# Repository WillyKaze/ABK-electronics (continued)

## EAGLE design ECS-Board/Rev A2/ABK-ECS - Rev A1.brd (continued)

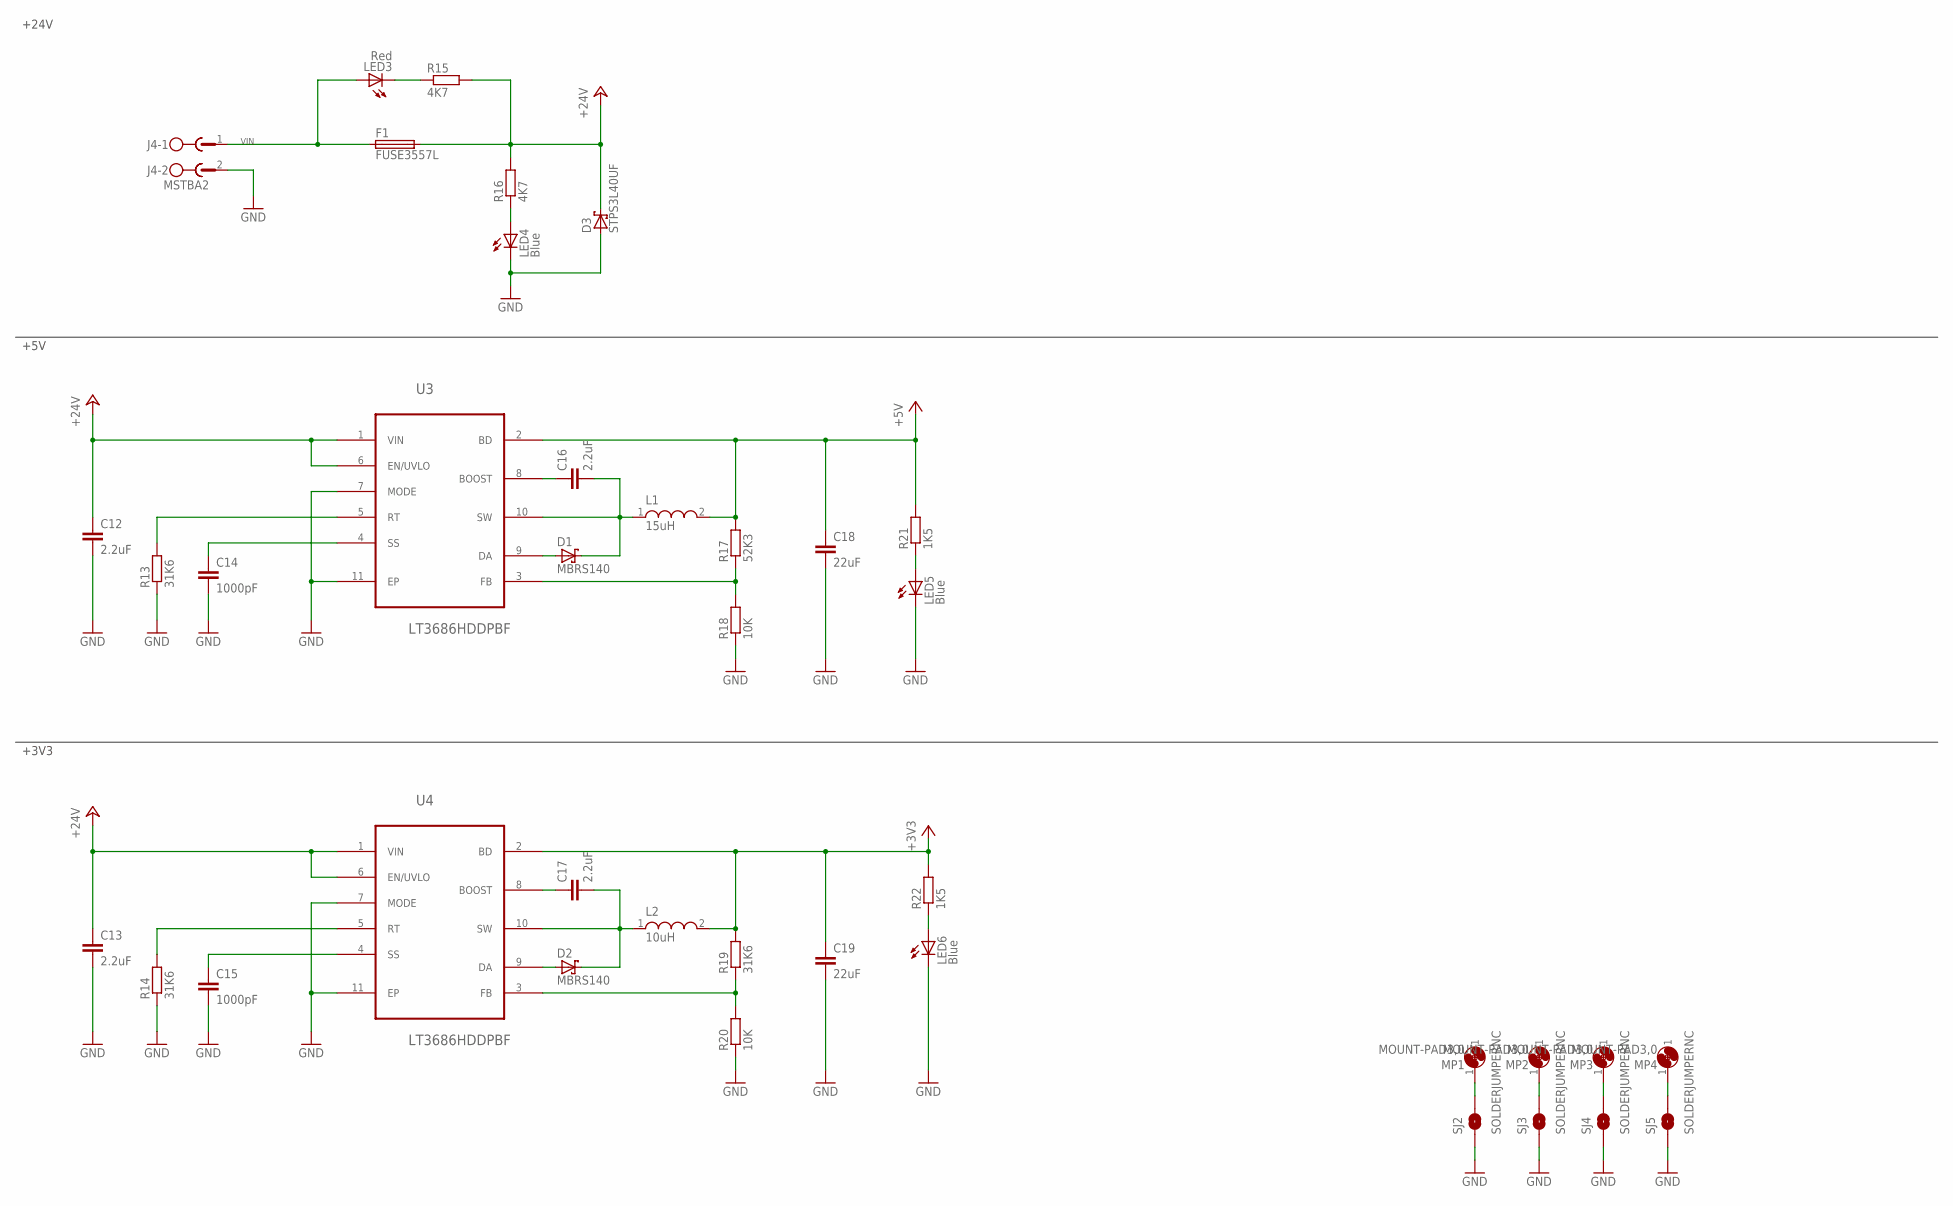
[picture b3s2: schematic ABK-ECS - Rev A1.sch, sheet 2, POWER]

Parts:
C12, C13, C16, C17: 2.2uF; C0603; MPN GRT188R61H225KE13D
C14, C15: 1000pF; C0603; MPN MC0603B102K500CT
C18, C19: 22uF; C0805; MPN MCMT21N220F250CT
D1, D2: MBRS140; DO-214AA; MPN MBRS140T3G
D3: STPS3L40UF; SMB
F1: FUSE3557L; 3557-LITTLE; MPN 3557
J4: MSTBA2
L1: 15uH; WE-PD2_5848/5820; MPN 744774115
L2: 10uH; WE-PD2_5848/5820; MPN 74477410
LED3: Red; CHIPLED_0603; MPN OVS-0603
LED4: Blue; CHIPLED_0603; MPN OVS-0603
LED5, LED6: Blue; CHIP-LED0603; MPN OVS-0603
MP1, MP2, MP3, MP4: MOUNT-PAD3,0; P3,0
R13, R14, R19: 31K6; R0603; MPN MCMR06X3162FTL
R15, R16: 4K7; R0603; MPN MCMR06X4701FTL
R17: 52K3; R0603; MPN MC0063W0603152K3
R18, R20: 10K; R0603; MPN MCMR06X1002FTL
R21, R22: 1K5; R0603; MPN MCMR06X1501FTL
SJ2, SJ3, SJ4, SJ5: SOLDERJUMPERNC; SJ_2S
U3, U4: LT3686HDDPBF; DFN300X300X80-11N

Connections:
1: MP1.1, SJ2.2
2: MP2.1, SJ3.2
3: MP3.1, SJ4.2
4: MP4.1, SJ5.2
+3V3: C19.1, L2.2, R19.2, R22.2, U4.2 (BD); also elsewhere on the board
+5V: C18.1, L1.2, R17.2, R21.2, U3.2 (BD); also elsewhere on the board
+24V: C12.1, C13.1, D3.C, F1.3 (2), F1.4 (2), R15.2, R16.2, U3.1 (VIN), U3.6 (EN/UVLO), U4.1 (VIN), U4.6 (EN/UVLO); also elsewhere on the board
GND: C12.2, C13.2, C14.2, C15.2, C18.2, C19.2, D3.A, J4.2, LED4.C, LED5.C, LED6.C, R13.1, R14.1, R18.1, R20.1, SJ2.1, SJ3.1, SJ4.1, SJ5.1, U3.7 (MODE), U3.11 (EP), U4.7 (MODE), U4.11 (EP); also elsewhere on the board
unnamed: R13.2, U3.5 (RT)
unnamed: C14.1, U3.4 (SS)
unnamed: R14.2, U4.5 (RT)
unnamed: C15.1, U4.4 (SS)
unnamed: R17.1, R18.2, U3.3 (FB)
unnamed: C16.1, U3.8 (BOOST)
unnamed: C16.2, D1.C, L1.1, U3.10 (SW)
unnamed: D1.A, U3.9 (DA)
unnamed: R19.1, R20.2, U4.3 (FB)
unnamed: C17.1, U4.8 (BOOST)
unnamed: C17.2, D2.C, L2.1, U4.10 (SW)
unnamed: D2.A, U4.9 (DA)
unnamed: LED4.A, R16.1
unnamed: LED3.C, R15.1
unnamed: LED6.A, R22.1
unnamed: LED5.A, R21.1
VIN: F1.1, F1.2 (1), J4.1, LED3.A

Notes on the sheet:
+5V
+3V3
+24V

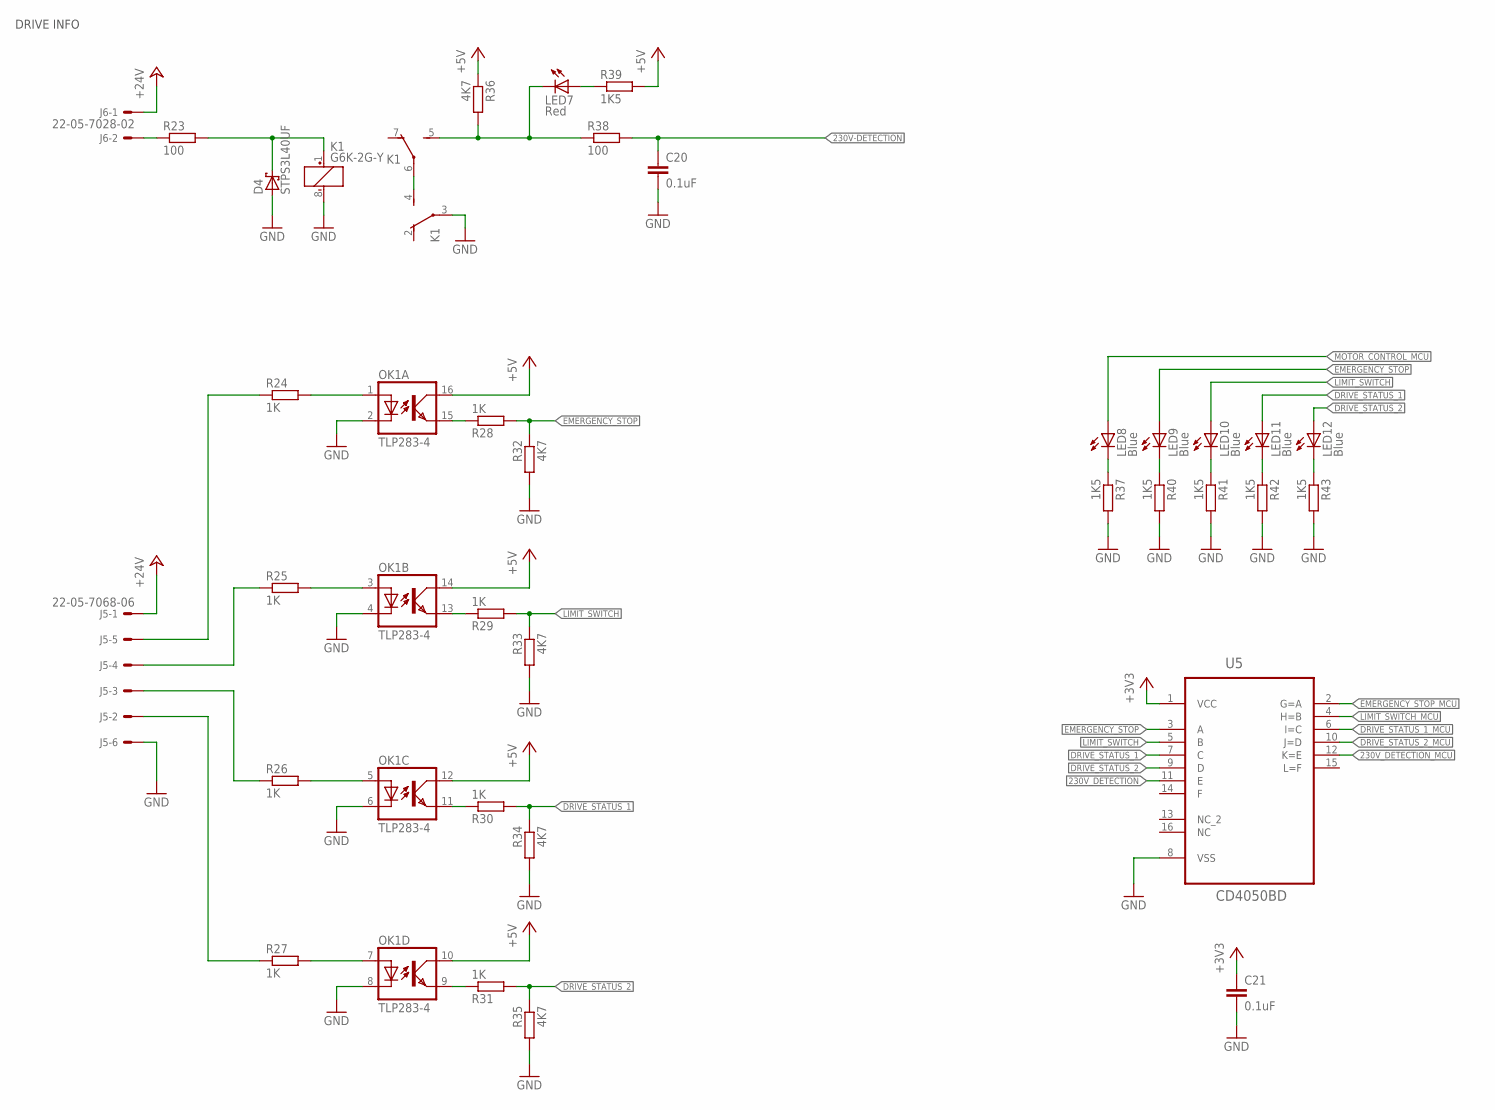
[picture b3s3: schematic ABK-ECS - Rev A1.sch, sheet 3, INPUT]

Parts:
C20, C21: 0.1uF; C0603; MPN MC0603B104K160CT
D4: STPS3L40UF; SMB
J5: 22-05-7068-06; 7395-06; MPN 22-05-7068
J6: 22-05-7028-02; 7395-02; MPN 22-05-7028
K1: G6K-2G-Y; MPN G6K-2G-Y 24DC
LED7: Red; CHIPLED_0603; MPN OVS-0603
LED8, LED9, LED10, LED11, LED12: Blue; CHIPLED_0603; MPN OVS-0603
OK1: TLP283-4; MINI-FLAT-16; MPN TCMT4100
R23, R38: 100; R0603; MPN MCMR06X1000FTL
R24, R25, R26, R27, R28, R29, R30, R31: 1K; R0603; MPN MCMR06X1001FTL
R32, R33, R34, R35, R36: 4K7; R0603; MPN MCMR06X4701FTL
R37, R39, R40, R41, R42, R43: 1K5; R0603; MPN MCMR06X1501FTL
U5: CD4050BD; SOIC127P600X175-16N

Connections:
230V-DETECTION: C20.1, R38.2; also elsewhere on the board
230V_DETECTION: U5.11 (E)
230V_DETECTION_MCU: U5.12 (K=E); also elsewhere on the board
+3V3: C21.1, U5.1 (VCC); also elsewhere on the board
+5V: OK1.10 (COL), OK1.12 (COL), OK1.14 (COL), OK1.16 (COL), R36.1, R39.2; also elsewhere on the board
+24V: J5.1, J6.1; also elsewhere on the board
DRIVE_STATUS_1: LED11.A, R30.2, R34.1, U5.7 (C)
DRIVE_STATUS_1_MCU: U5.6 (I=C); also elsewhere on the board
DRIVE_STATUS_2: LED12.A, R31.2, R35.1, U5.9 (D)
DRIVE_STATUS_2_MCU: U5.10 (J=D); also elsewhere on the board
EMERGENCY_STOP: LED9.A, R28.2, R32.1, U5.3 (A)
EMERGENCY_STOP_MCU: U5.2 (G=A); also elsewhere on the board
GND: C20.2, C21.2, D4.A, J5.6, K1.3, K1.8 (-), OK1.2 (C), OK1.4 (C), OK1.6 (C), OK1.8 (C), R32.2, R33.2, R34.2, R35.2, R37.2, R40.2, R41.2, R42.2, R43.2, U5.8 (VSS); also elsewhere on the board
LIMIT_SWITCH: LED10.A, R29.2, R33.1, U5.5 (B)
LIMIT_SWITCH_MCU: U5.4 (H=B); also elsewhere on the board
MOTOR_CONTROL_MCU: LED8.A; also elsewhere on the board
unnamed: D4.C, K1.1 (+), R23.2
unnamed: J6.2, R23.1
unnamed: OK1.1 (A), R24.2
unnamed: OK1.3 (A), R25.2
unnamed: OK1.5 (A), R26.2
unnamed: OK1.7 (A), R27.2
unnamed: J5.2, R27.1
unnamed: J5.3, R26.1
unnamed: J5.4, R25.1
unnamed: J5.5, R24.1
unnamed: LED8.C, R37.1
unnamed: LED9.C, R40.1
unnamed: LED10.C, R41.1
unnamed: LED11.C, R42.1
unnamed: K1.4 (S), K1.6
unnamed: OK1.9 (EMIT), R31.1
unnamed: OK1.11 (EMIT), R30.1
unnamed: OK1.13 (EMIT), R29.1
unnamed: OK1.15 (EMIT), R28.1
unnamed: LED12.C, R43.1
unnamed: K1.5 (S), LED7.C, R36.2, R38.1
unnamed: LED7.A, R39.1

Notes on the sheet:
DRIVE INFO

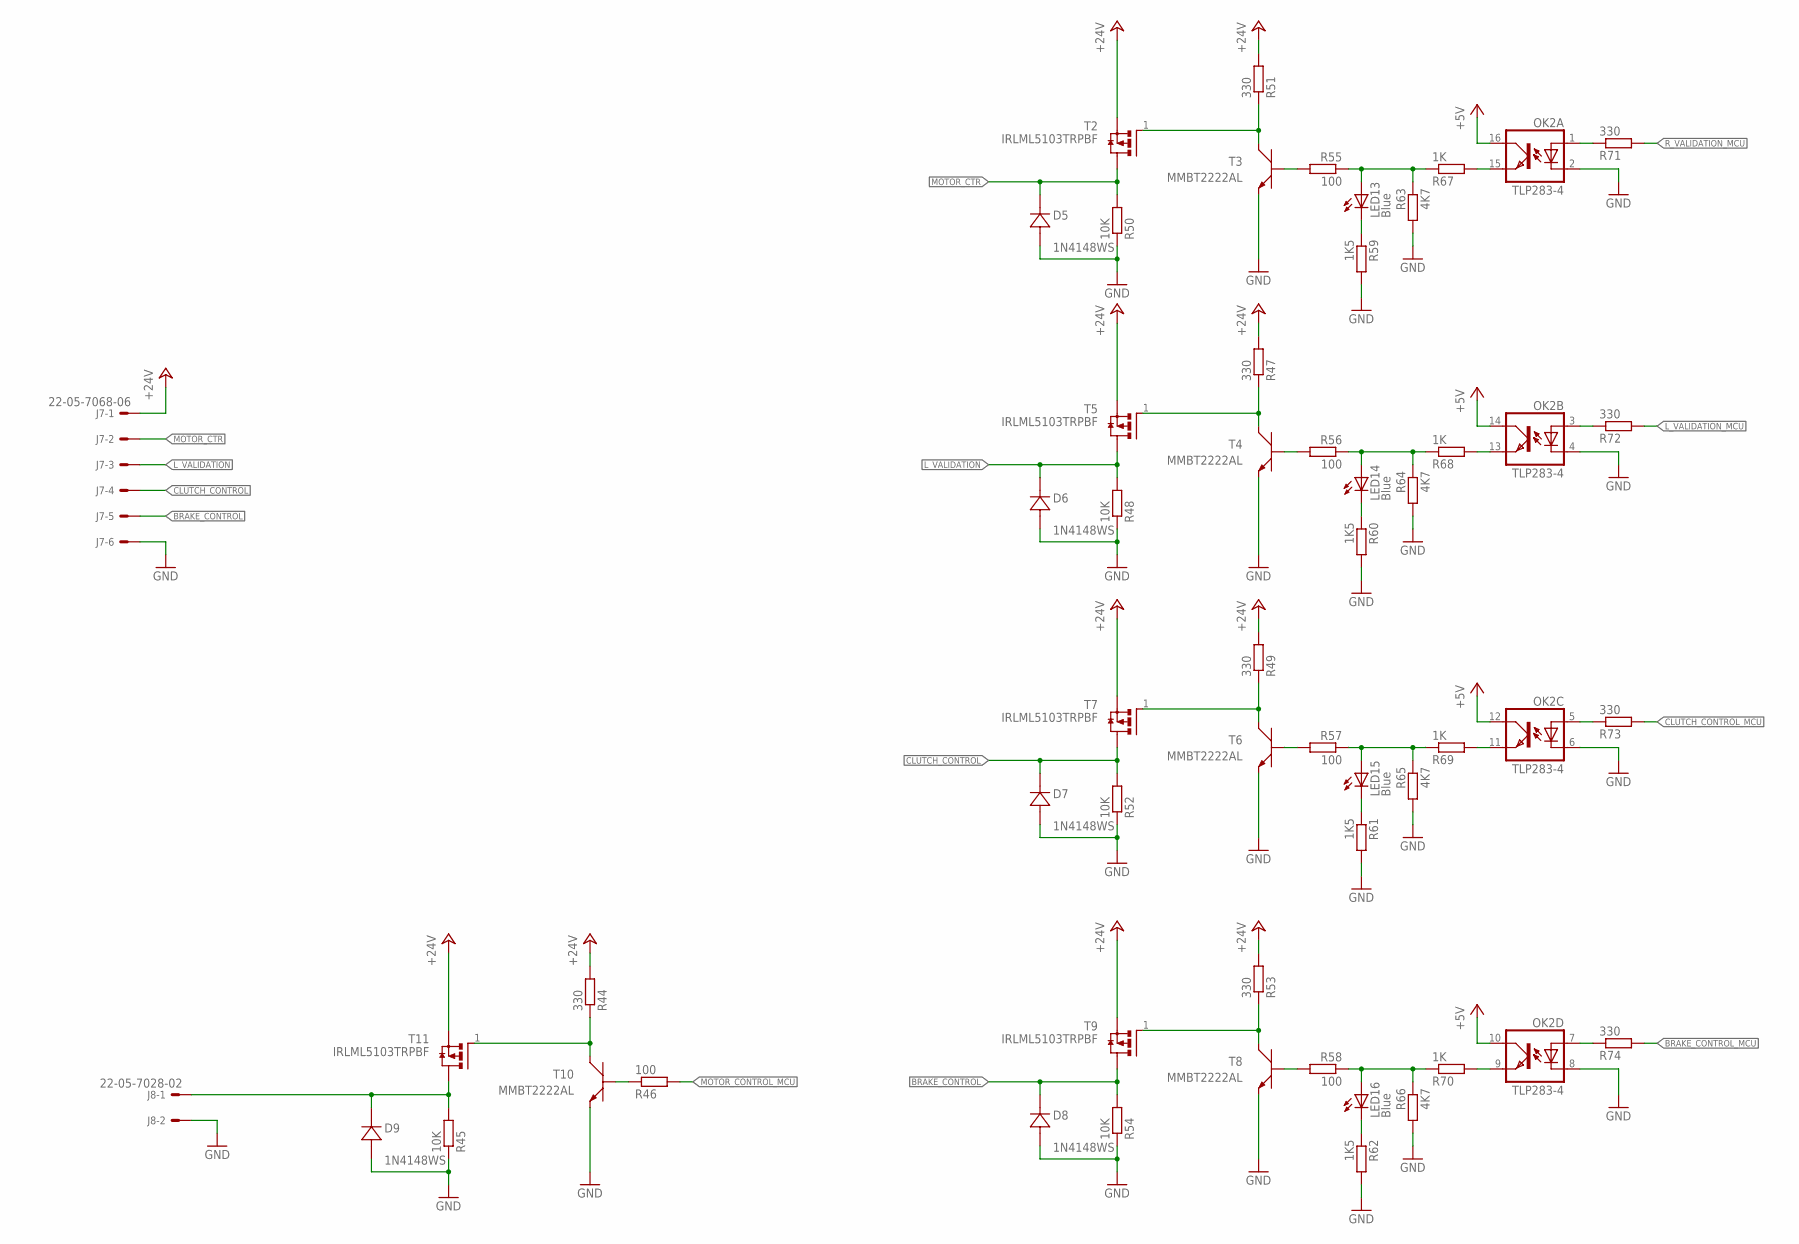
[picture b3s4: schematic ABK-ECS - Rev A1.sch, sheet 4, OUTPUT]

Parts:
D5, D6, D7, D8, D9: 1N4148WS; SOD323-W
J7: 22-05-7068-06; 7395-06; MPN 22-05-7068
J8: 22-05-7028-02; 7395-02; MPN 22-05-7028
LED13, LED14, LED15, LED16: Blue; CHIPLED_0603; MPN OVS-0603
OK2: TLP283-4; MINI-FLAT-16; MPN TCMT4100
R44, R47, R49, R51, R53: 330; R0603; MPN MCMR06X4701FTL
R45, R48, R50, R52, R54: 10K; R0603; MPN MCMR06X4701FTL
R46, R55, R56, R57, R58: 100; R0603; MPN MCMR06X1000FTL
R59, R60, R61, R62: 1K5; R0603; MPN MCMR06X1501FTL
R63, R64, R65, R66: 4K7; R0603; MPN MCMR06X4701FTL
R67, R68, R69, R70: 1K; R0603; MPN MCMR06X1001FTL
R71, R72, R73, R74: 330; R0603; MPN MCMR06X3300FTL
T2, T5, T7, T9, T11: IRLML5103TRPBF; SOT95P240X112-3N
T3, T4, T6, T8, T10: MMBT2222AL; SOT−23

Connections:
+5V: OK2.10 (COL), OK2.12 (COL), OK2.14 (COL), OK2.16 (COL); also elsewhere on the board
+24V: J7.1, R44.2, R47.2, R49.2, R51.2, R53.2, T2.2 (S), T5.2 (S), T7.2 (S), T9.2 (S), T11.2 (S); also elsewhere on the board
BRAKE_CONTROL: D8.C (1), J7.5, R54.2, T9.3 (D)
BRAKE_CONTROL_MCU: R74.2; also elsewhere on the board
CLUTCH_CONTROL: D7.C (1), J7.4, R52.2, T7.3 (D)
CLUTCH_CONTROL_MCU: R73.2; also elsewhere on the board
GND: D5.A (2), D6.A (2), D7.A (2), D8.A (2), D9.A (2), J7.6, J8.2, OK2.2 (C), OK2.4 (C), OK2.6 (C), OK2.8 (C), R45.1, R48.1, R50.1, R52.1, R54.1, R59.2, R60.2, R61.2, R62.2, R63.2, R64.2, R65.2, R66.2, T3.2 (E), T4.2 (E), T6.2 (E), T8.2 (E), T10.2 (E); also elsewhere on the board
L_VALIDATION: D6.C (1), J7.3, R48.2, T5.3 (D)
L_VALIDATION_MCU: R72.2; also elsewhere on the board
MOTOR_CONTROL_MCU: R46.2; also elsewhere on the board
MOTOR_CTR: D5.C (1), J7.2, R50.2, T2.3 (D)
unnamed: R55.2, T3.1 (B)
unnamed: R51.1, T2.1 (G), T3.3 (C)
unnamed: R56.2, T4.1 (B)
unnamed: R47.1, T4.3 (C), T5.1 (G)
unnamed: R57.2, T6.1 (B)
unnamed: R49.1, T6.3 (C), T7.1 (G)
unnamed: R58.2, T8.1 (B)
unnamed: R53.1, T8.3 (C), T9.1 (G)
unnamed: R46.1, T10.1 (B)
unnamed: R44.1, T10.3 (C), T11.1 (G)
unnamed: D9.C (1), J8.1, R45.2, T11.3 (D)
unnamed: LED13.A, R55.1, R63.1, R67.1
unnamed: OK2.15 (EMIT), R67.2
unnamed: LED14.A, R56.1, R64.1, R68.1
unnamed: OK2.13 (EMIT), R68.2
unnamed: LED15.A, R57.1, R65.1, R69.1
unnamed: LED16.A, R58.1, R66.1, R70.1
unnamed: OK2.11 (EMIT), R69.2
unnamed: OK2.9 (EMIT), R70.2
unnamed: OK2.1 (A), R71.1
unnamed: OK2.3 (A), R72.1
unnamed: OK2.7 (A), R74.1
unnamed: OK2.5 (A), R73.1
unnamed: LED13.C, R59.1
unnamed: LED14.C, R60.1
unnamed: LED15.C, R61.1
unnamed: LED16.C, R62.1
R_VALIDATION_MCU: R71.2; also elsewhere on the board

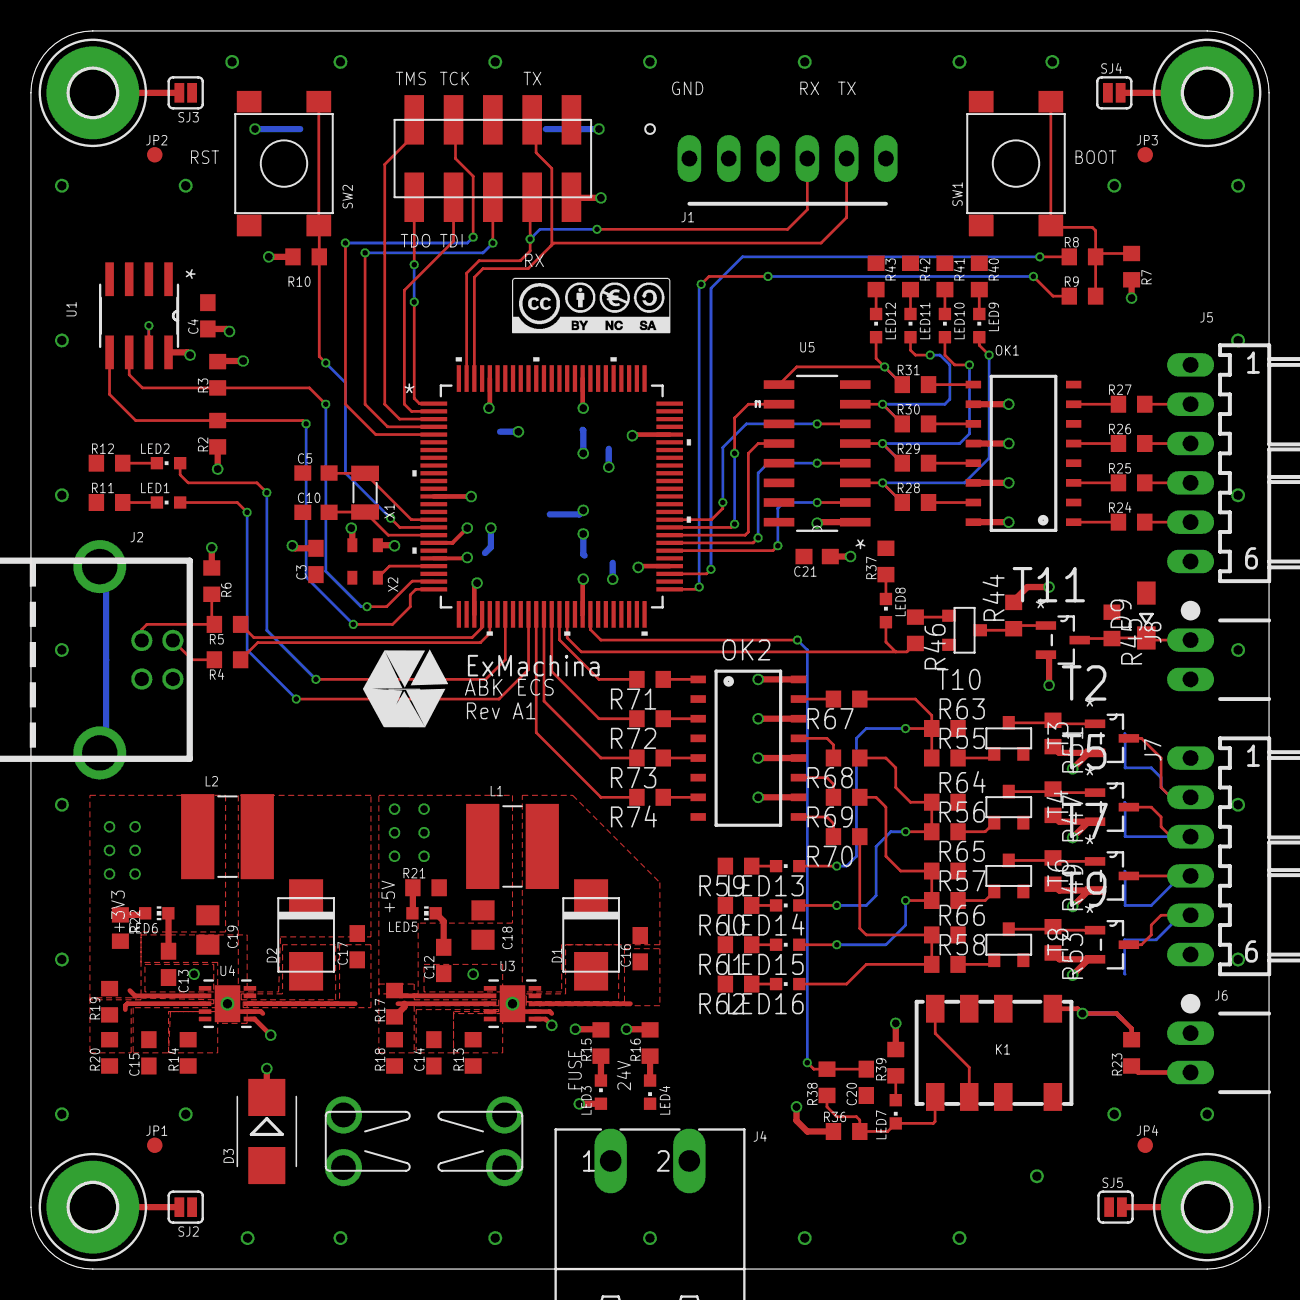
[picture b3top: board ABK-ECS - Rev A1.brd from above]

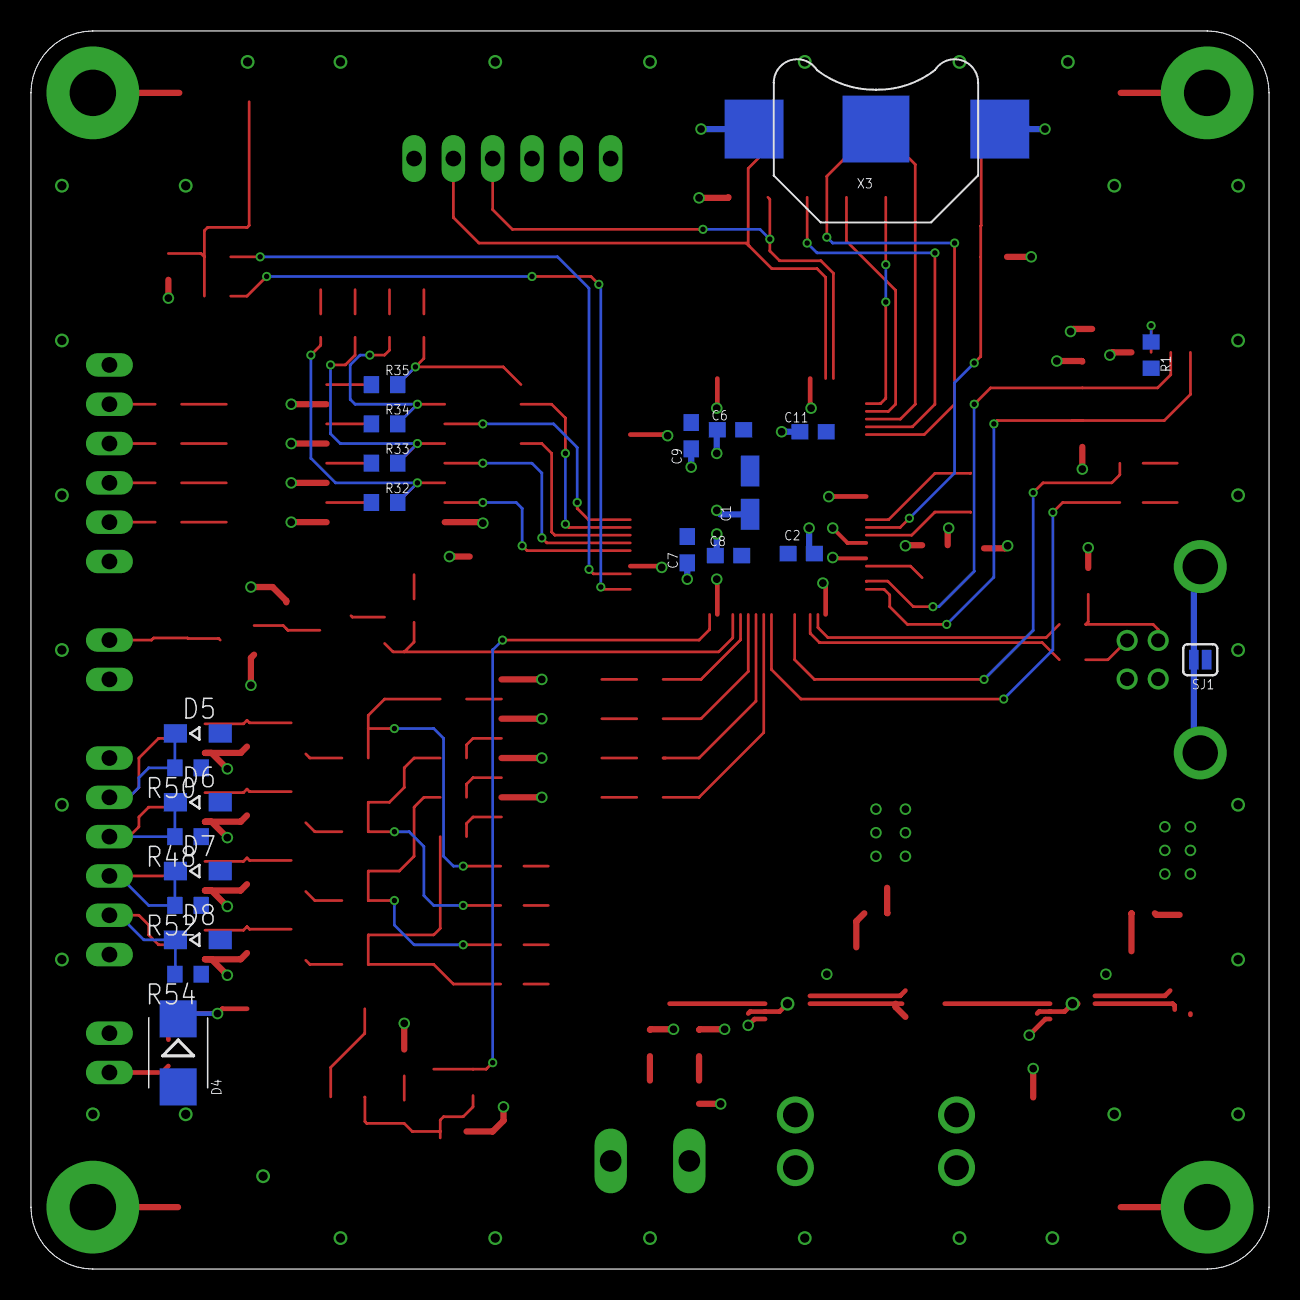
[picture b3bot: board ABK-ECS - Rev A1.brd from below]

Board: 4 copper layers, 80.0 x 80.0 mm, 169 parts (23 on the bottom side), 121 nets.

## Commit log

2017-02-28 Clean repos
2017-02-28 Rename folder
2017-02-28 Change readme and description files
2017-03-07 Update MPN and generate part list
2017-05-30 Update MDP folder
2017-05-30 Modify ECS board with pull-down output
2017-07-18 Add rev A2 and modify board
2017-08-31 Add input and output to the board and LDO 5V to 3.3V for FTDI connector
2017-09-05 Rotate board 90 degres
2017-09-05 Add 24V and Vin poly for the fuse
2017-09-05 Add pullup resistor on AT24C WP Separate +5V from ISP connector and the +5V general and add a diode Change +5V--->+3V3 conversion methode on input Wired OK2D
2017-09-06 Resize and place all name and value of the component of the board
2017-09-07 Final modifications before production version:
    * Rename inputs and outputs to generic names
    * Add silkscreen labels
    * Move components for better layout in output block
2017-09-07 Update componenets from eagle-resources
2017-09-07 Update from eagle-resources
    * Modified footprints
2017-09-08 Minor route upgrade
2017-09-13 Generate Gerber and MDP files
2017-10-10 Replace output resistance and fuse LED
2017-11-13 Rev A2-a : Change pullup resistors of the outputs to 10k, Inverse 100 and 1k resistors after the opto
2017-11-14 Add Rev A3 files
    - Add new connectors for ICSP/JTAG
    - Improve auto ISP
2017-11-14 Propagate changes from Rev A2a to Rev A3
2017-11-28 Convert text to vector and update silkscreen
2017-11-29 Create rev B1 : - Change output pull-down to 1K with 1206 footprint - Add USB Connect interface and add V Bus projection
2017-11-30 Place and route ethernet interface
2017-11-30 Route JTAG, ISCP and LED On board
2017-11-30 Route ethernet LED and Reset signal
2017-12-04 Finish to route the board
2017-12-05 Add 0R to the USB Pull-up
2017-12-06 Routing improvement
2017-12-07 Resize board 100x100mm
2017-12-07 Remape I/O and add UART-I2C-2ADC-Encoder mcu pin
2017-12-08 dd pull up and pull down resistor to I2C and UART and place every compoment
2017-12-08 Route USB LED, re-place IO leds
2017-12-11 Route Input
2017-12-11 Route Outputs and Encoder Inputs
2017-12-11 Route UART and I2C
2017-12-11 Route ADC
2017-12-11 Route the output
2017-12-11 Re-Map MCU output signal
2017-12-11 Move RTC battery holder and route VBAT, Boot signals and Leds signals
2017-12-11 Route Reset and all airwire
2017-12-13 Improte routing and add Silkscreen
2017-12-20 Final changes before manufacturing:
    - Update silkscreen:
    * Place labels for each pin
    * Update USB silkscreen
    * Update RJ45 silkscreen
    * Update +24V socket silkscreen
    * Update battery holder silscreen
2017-12-20 Add and route decoupling power for VADC
2018-01-09 Generated MDP files
